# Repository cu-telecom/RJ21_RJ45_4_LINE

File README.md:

# RJ21_RJ45_4_LINE

A simple breakout board that exposes 4 lines from an RJ21 connector. Designed for testing and configuring devices without requiring a bulky cable.

## License 

MIT License

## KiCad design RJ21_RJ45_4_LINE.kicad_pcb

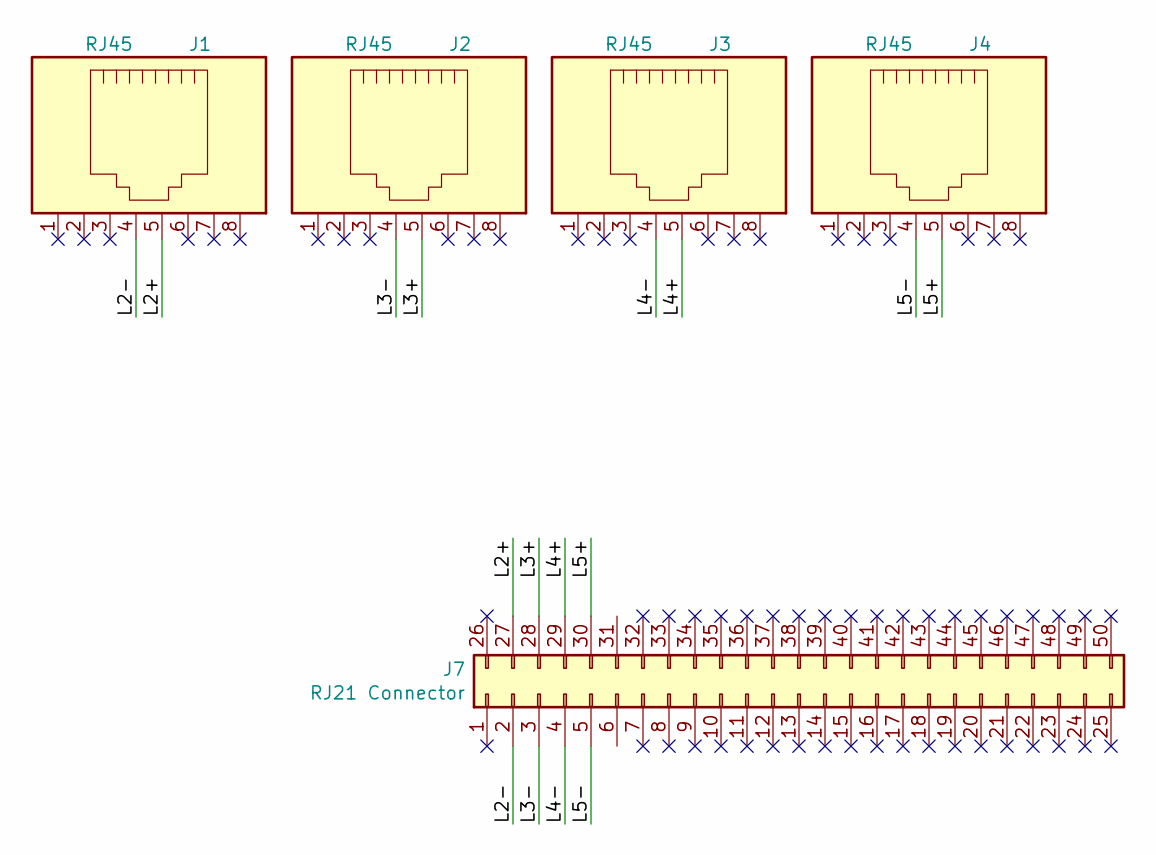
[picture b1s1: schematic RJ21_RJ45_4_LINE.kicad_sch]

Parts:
J1, J2, J3, J4: RJ45; RJ45_OST_PJ012-8P8CX_Vertical
J7: RJ21 Connector; AliExpress_RJ21

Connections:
/L2+: J1.5, J7.27
/L2-: J1.4, J7.2
/L3+: J2.5, J7.28
/L3-: J2.4, J7.3
/L4+: J3.5, J7.29
/L4-: J3.4, J7.4
/L5+: J4.5, J7.30
/L5-: J4.4, J7.5

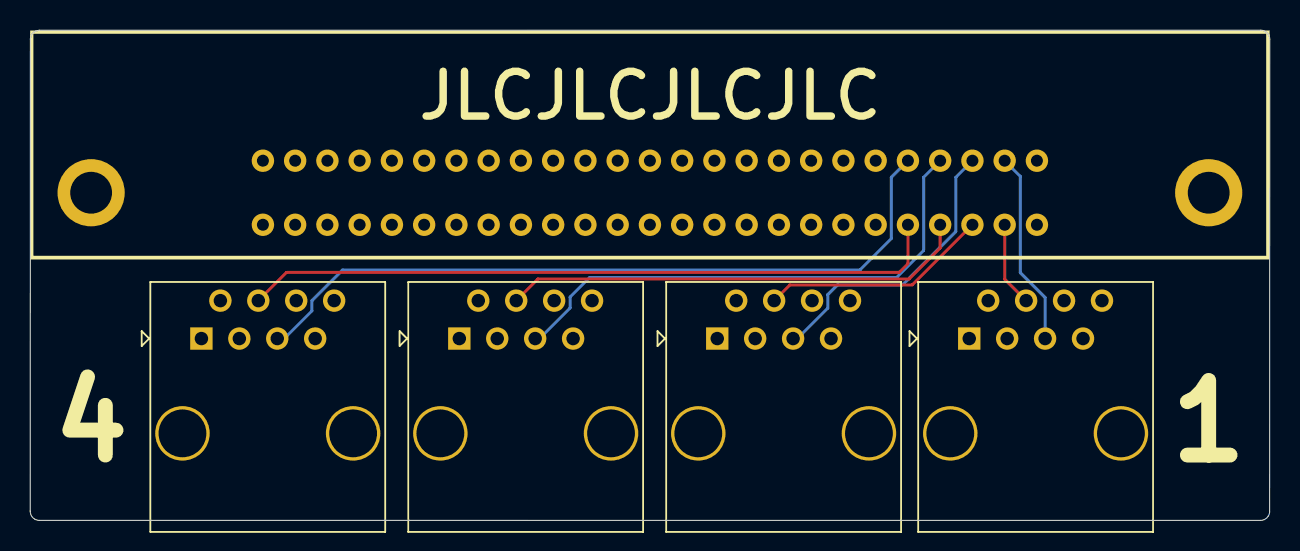
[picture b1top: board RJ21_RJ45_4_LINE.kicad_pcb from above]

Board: 2 copper layers, 83.0 x 32.8 mm, 5 parts (0 on the bottom side), 8 nets.

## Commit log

2024-01-05 init
2024-01-05 add gerbers
2024-01-05 Produce Gerbers
